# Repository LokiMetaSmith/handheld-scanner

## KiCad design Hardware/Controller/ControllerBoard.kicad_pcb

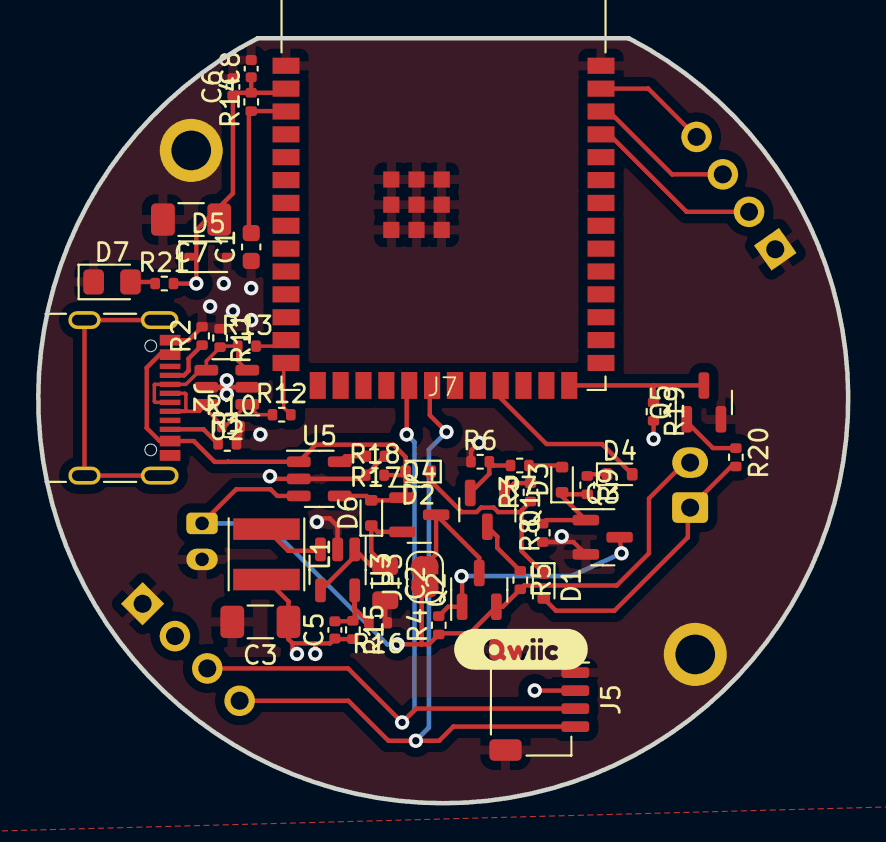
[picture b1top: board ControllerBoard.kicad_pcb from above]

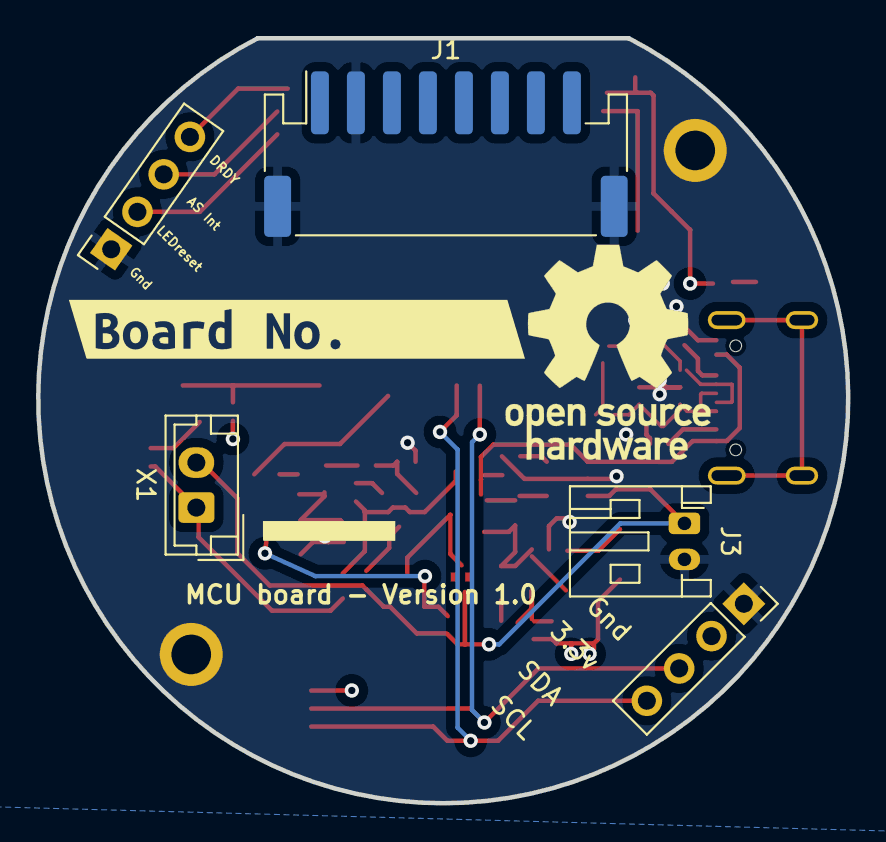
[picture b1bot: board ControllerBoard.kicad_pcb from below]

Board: 4 copper layers, 45.0 x 42.5 mm, 56 parts (6 on the bottom side), 34 nets.

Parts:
C1: 2u; C_0603_1608Metric
C2: 4.7u; C_0805_2012Metric
C3, C7: 10u; C_1206_3216Metric_Pad1.33x1.80mm_HandSolder
C5: 6.8p; C_0402_1005Metric
C6: 0.01u; C_0402_1005Metric
C8: 0.1u; C_0402_1005Metric
D1, D2, D3, D4, D6: BAS516; D_SOD-523
D5: 3.3v_TVS; D_SOD-323
D7: POWER LED; LED_0805_2012Metric_Pad1.15x1.40mm_HandSolder
J1: Conn_01x08_MountingPin; JST_PH_S8B-PH-SM4-TB_1x08-1MP_P2.00mm_Horizontal
J2: USB_C_Receptacle_USB2.0; USB_C_Receptacle_GCT_USB4105-xx-A_16P_TopMnt_Horizontal
J3: Conn_01x02_Male; JST_PH_S2B-PH-K_1x02_P2.00mm_Horizontal
J5: I2C; JST_SH_SM04B-SRSS-TB_1x04-1MP_P1.00mm_Horizontal
J7: Conn_01x09; round_notch
JP3: Jumper_2_Open; SolderJumper-2_P1.3mm_Bridged2Bar_RoundedPad1.0x1.5mm
L1: 2.2uH; L_Taiyo-Yuden_MD-4040
LOGO1: OSHW-Logo_11.4x12mm_SilkScreen
LOGO2: PlasticScannerLogo
Q1, Q3, Q5: BC818; SOT-23
Q2, Q4: AO3401A; SOT-23
R1, R2, R17: 5.1k; R_0402_1005Metric
R3, R20, R21: 1k; R_0402_1005Metric
R4, R8, R18: 100k; R_0402_1005Metric
R5, R7: 10k; R_0402_1005Metric
R6: 220k; R_0402_1005Metric
R9: 220; R_0402_1005Metric
R10, R11: 15K; R_0402_1005Metric
R12, R13: 27; R_0402_1005Metric
R14, R19: 10K; R_0402_1005Metric
R15: 680k; R_0402_1005Metric
R16: 150K; R_0402_1005Metric
U1: ESP32-S3-WROOM-1
U2: SN65220; SOT-23-6
U3: TLV62569DBV; SOT-23-5
U5: MCP73811T-420I-OT; SOT-23-5
X1: CON_JST_PH_2PIN_MTPH2; JST_EH_B2B-EH-A_1x02_P2.50mm_Vertical
kibuzzard-6398DD41: G***; kibuzzard-6398DD41
kibuzzard-6346913B: G***; kibuzzard-6346913B

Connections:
+3V3: C3.1, C5.1, C6.1, C7.1, C8.1, D5.1 (A1), J5.2, J7.2, L1.2, R14.2, R15.2, R19.2, R21.2, U1.2 (3V3)
/AS7341_INT: J7.7, U1.38 (GPIO2/TOUCH2/ADC1_CH1)
/D+: J2.A6 (D+), J2.B6 (D+), R10.1, R12.1, U2.1, U2.6 (A)
/D-: J2.A7 (D-), J2.B7 (D-), R11.2, R13.1, U2.3, U2.4 (B)
/DRDY_INT: J7.8, U1.39 (GPIO1/TOUCH1/ADC1_CH0)
/EN: C1.2, R14.1, U1.3 (EN)
/KeepAlive: D4.2 (A), U1.23 (GPIO21)
/LED_RESET: J7.6, U1.37 (U0TXD/GPIO43/CLK_OUT1)
/Switched_Power: C2.1, D6.1 (K), Q4.2 (S), U3.1 (EN), U3.4 (VIN)
/Trigger: Q5.2 (E), R19.1, U1.26 (GPIO45)
/Trigger_Wake_Up/VBAT: J3.1, JP3.1 (A), Q2.2 (S), R4.1, R5.2, U5.3 (VBAT), X1.2
/USB_D+: R12.2, U1.14 (GPIO20/U1CTS/ADC2_CH9/CLK_OUT1/USB_D+)
/USB_D-: R13.2, U1.13 (GPIO19/U1RTS/ADC2_CH8/CLK_OUT2/USB_D-)
/USB_pwr: D2.2 (A), D6.2 (A), J2.A4 (VBUS), J2.A9 (VBUS), J2.B4 (VBUS), J2.B9 (VBUS), Q4.1 (G), R18.2, U5.1 (CEN), U5.4 (VDD)
GND: C1.1, C2.2, C3.2, C6.2, C7.2, C8.2, D5.2 (A2), D7.1 (K), J1.2, J1.MP (MountPin), J2.A1 (GND), J2.A12 (GND), J2.B1 (GND), J2.B12 (GND), J3.2, J5.1, J5.MP (Pin_5), J7.1, J7.5, J7.MP, Q3.2 (E), Q5.1 (B), R1.2, R2.2, R6.1, R8.1, R10.2, R11.1, R16.1, R17.1, R18.1, U1.1 (GND), U1.40 (GND), U1.41 (GND), U2.2 (GND), U2.5 (GND), U3.2 (GND), U5.2 (VSS)
unnamed: D1.2 (A), R20.1, X1.1
unnamed: D1.1 (K), D2.1 (K), R3.1
unnamed: D3.2 (A), R7.1
unnamed: D3.1 (K), Q3.1 (B), R8.2, R9.2
unnamed: D4.1 (K), R9.1
unnamed: D7.2 (A), R21.1
unnamed: J2.A5 (CC1), R2.1
unnamed: J2.B5 (CC2), R1.1
unnamed: JP3.2 (B), Q2.3 (D), Q4.3 (D)
unnamed: Q1.1 (B), R3.2
unnamed: Q1.3 (C), R5.1
unnamed: Q1.2 (E), R6.2, R7.2
unnamed: Q2.1 (G), Q3.3 (C), R4.2
unnamed: Q5.3 (C), R20.2
unnamed: C5.2, R15.1, R16.2, U3.5 (FB)
unnamed: L1.1, U3.3 (SW)
unnamed: R17.2, U5.5 (PROG)
SCL: J5.4, J7.4, U1.20 (GPIO12/TOUCH12/ADC2_CH1/FSPICLK/FSPIIO6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)
SDA: J5.3, J7.3, U1.19 (GPIO11/TOUCH11/ADC2_CH0/FSPID/FSPIIO5/S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)

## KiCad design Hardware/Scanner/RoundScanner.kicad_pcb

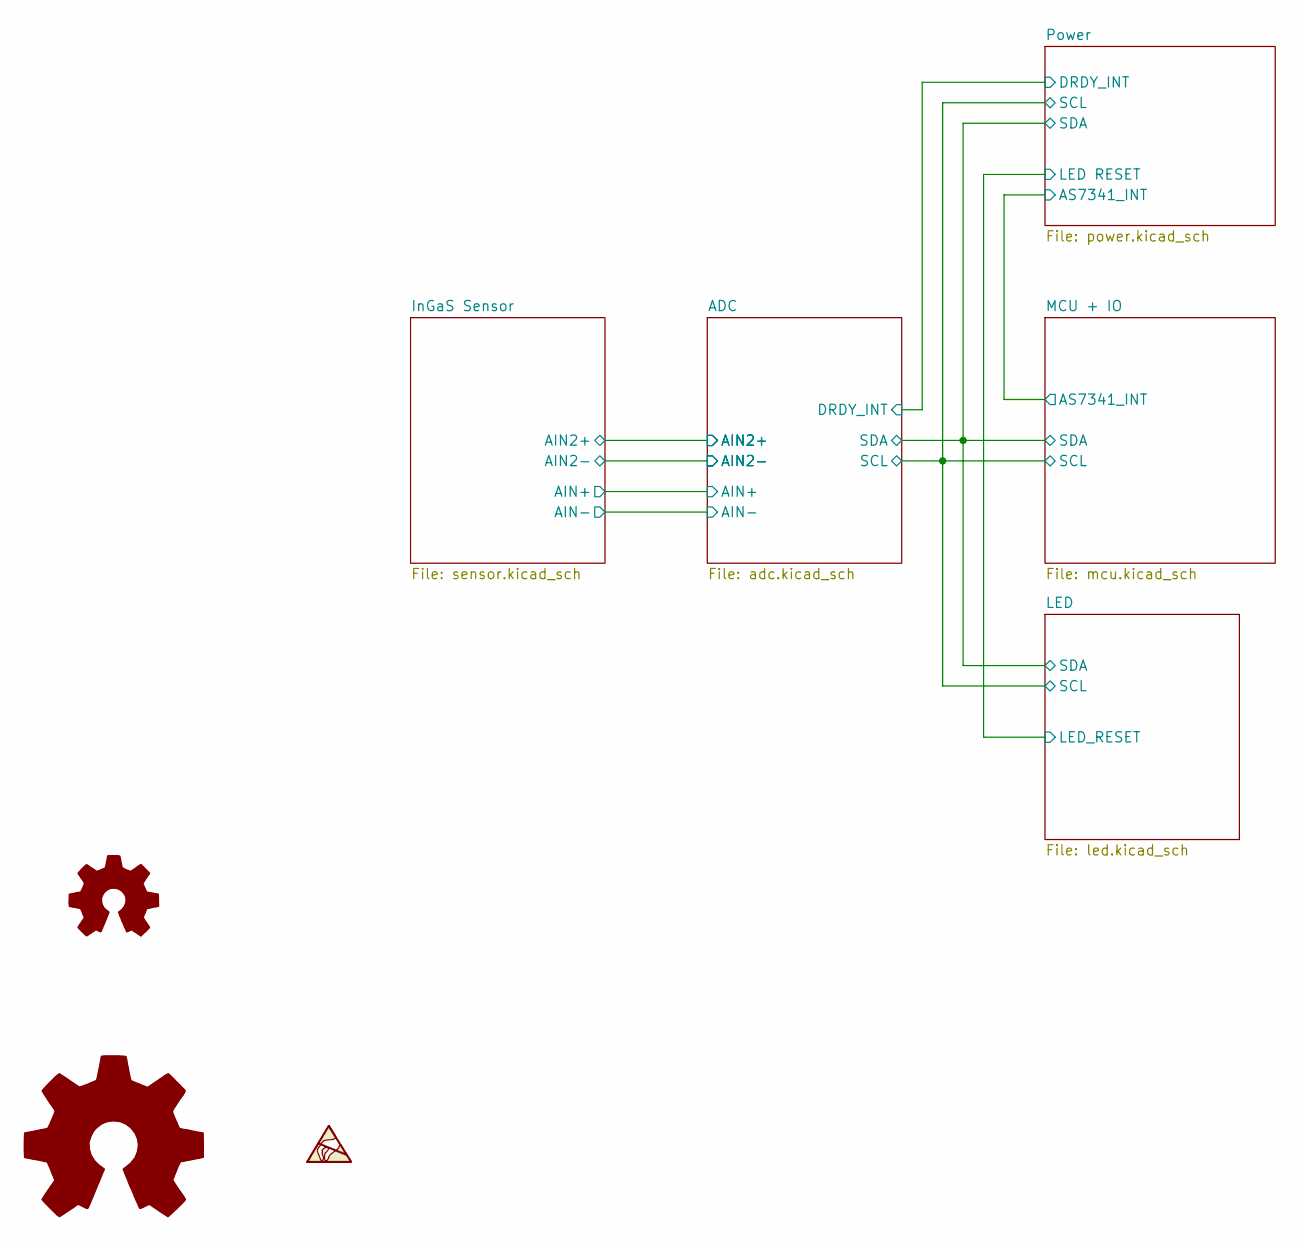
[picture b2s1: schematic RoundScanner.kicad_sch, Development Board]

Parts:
LOGO1: OSHW-Logo_11.4x12mm_SilkScreen
LOGO2: PlasticScannerLogo

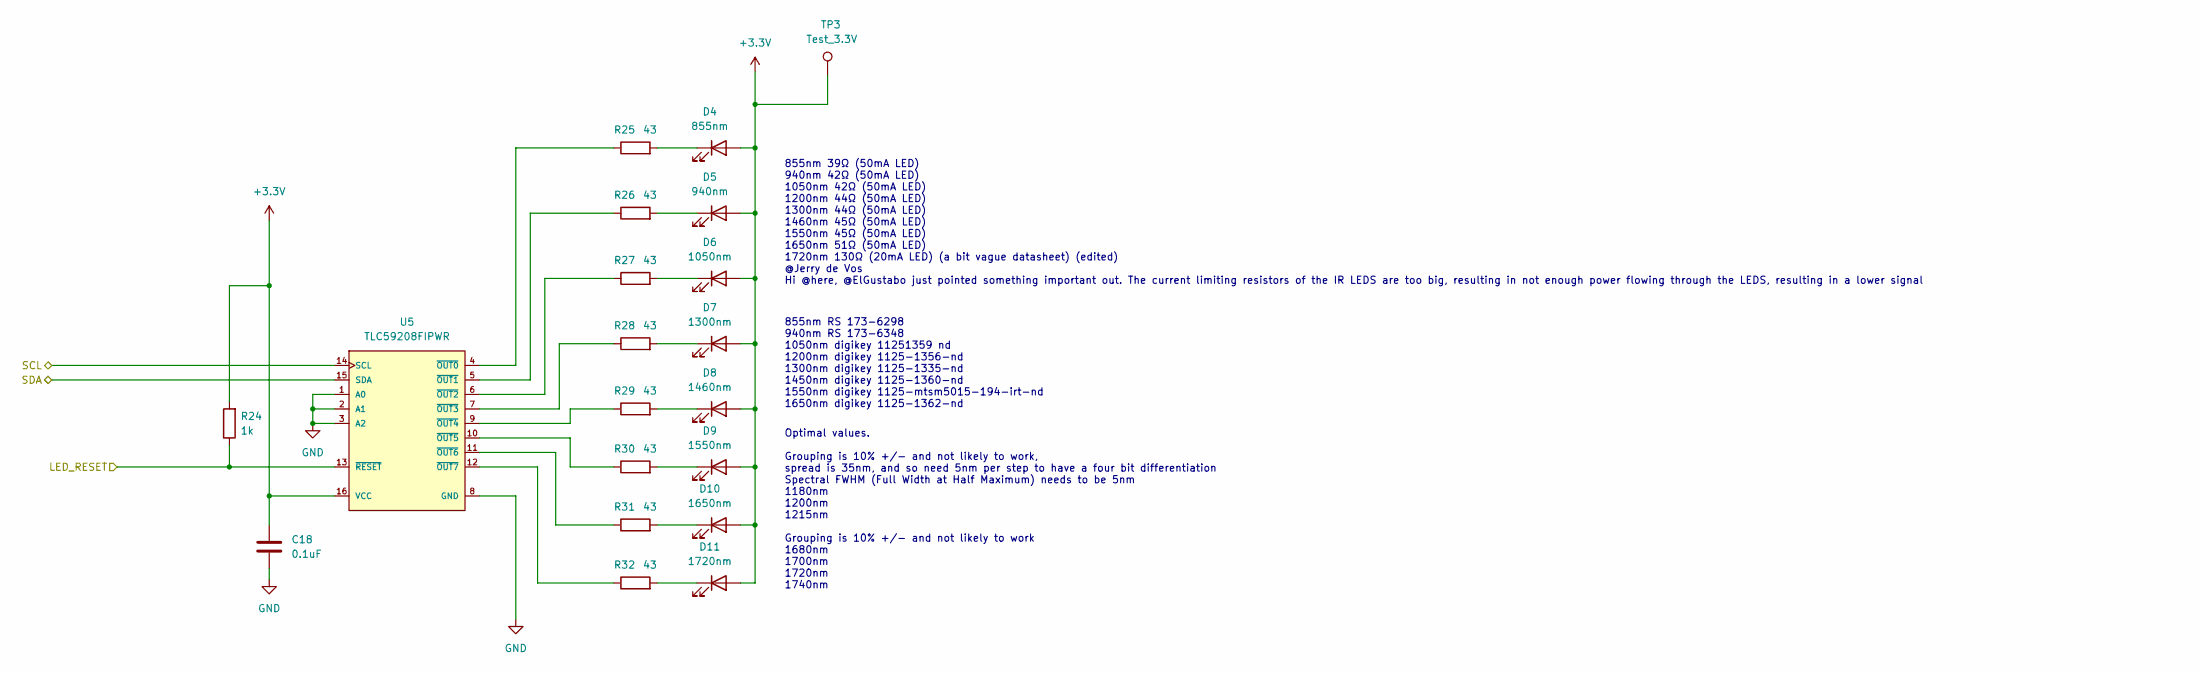
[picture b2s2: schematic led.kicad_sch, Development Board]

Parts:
C18: 0.1uF; C_0603_1608Metric_Pad1.08x0.95mm_HandSolder; digikey description CAP CER 0.1UF 16V X7R 0603
D4: 855nm; LED_1206_3216Metric_Pad1.42x1.75mm_HandSolder; digikey part number 1516-1269-1-ND
D5: 940nm; LED_1206_3216Metric_Pad1.42x1.75mm_HandSolder; digikey part number 1080-1350-1-ND
D6: 1050nm; LED_1206_3216Metric_Pad1.42x1.75mm_HandSolder; digikey part number 1125-1342-ND
D7: 1300nm; LED_1206_3216Metric_Pad1.42x1.75mm_HandSolder; digikey part number 5242-OIS-1501300N-X-TCT-ND
D8: 1460nm; LED_1206_3216Metric_Pad1.42x1.75mm_HandSolder; digikey part number 1125-MTSM6014-194-IRCT-ND
D9: 1550nm; LED_1206_3216Metric_Pad1.42x1.75mm_HandSolder; digikey part number 5242-OIS-1501550N-X-TCT-ND
D10: 1650nm; LED_1206_3216Metric_Pad1.42x1.75mm_HandSolder; digikey part number 1125-1354-ND
D11: 1720nm; LED_1206_3216Metric_Pad1.42x1.75mm_HandSolder; digikey part number 1125-MTSM0012-194-IRCT-ND
R24: 1k; R_0603_1608Metric_Pad0.98x0.95mm_HandSolder; digikey description RES 1K OHM 1% 1/10W 0603
R25, R26, R27, R28, R29, R30, R31: 43; R_0603_1608Metric_Pad0.98x0.95mm_HandSolder; digikey description RES SMD 43 OHM 5% 1/3W 0603
R32: 43; R_0603_1608Metric_Pad0.98x0.95mm_HandSolder; mouser part number 667-ERJ-3EKF1300V; digikey description RES SMD 43 OHM 5% 1/3W 0603
TP3: Test_3.3V; TestPoint_Pad_D1.5mm
U5: TLC59208FIPWR; SOP65P640X120-16N; digikey description TLC59208FIPWR

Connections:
/LED/LED_RESET: R24.1, U5.13 (~RESET); also elsewhere on the board
GND: C18.2, U5.1 (A0), U5.2 (A1), U5.3 (A2), U5.8 (GND); also elsewhere on the board
unnamed: D4.1 (K), R25.2
unnamed: D5.1 (K), R26.2
unnamed: D6.1 (K), R27.2
unnamed: D7.1 (K), R28.2
unnamed: D8.1 (K), R29.2
unnamed: D9.1 (K), R30.2
unnamed: D10.1 (K), R31.2
unnamed: D11.1 (K), R32.2
unnamed: R25.1, U5.4 (~OUT0)
unnamed: R26.1, U5.5 (~OUT1)
unnamed: R27.1, U5.6 (~OUT2)
unnamed: R28.1, U5.7 (~OUT3)
unnamed: R29.1, U5.9 (~OUT4)
unnamed: R30.1, U5.10 (~OUT5)
unnamed: R31.1, U5.11 (~OUT6)
unnamed: R32.1, U5.12 (~OUT7)
SCL: U5.14 (SCL); also elsewhere on the board
SDA: U5.15 (SDA); also elsewhere on the board

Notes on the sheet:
855nm RS 173-6298 940nm RS 173-6348 1050nm digikey 11251359 nd 1200nm digikey 1125-1356-nd 1300nm digikey 1125-1335-nd 1450nm digikey 1125-1360-nd 1550nm digikey 1125-mtsm5015-194-irt-nd 1650nm digikey 1125-1362-nd
855nm 39Ω (50mA LED) 940nm 42Ω (50mA LED) 1050nm 42Ω (50mA LED) 1200nm 44Ω (50mA LED) 1300nm 44Ω (50mA LED) 1460nm 45Ω (50mA LED) 1550nm 45Ω (50mA LED) 1650nm 51Ω (50mA LED) 1720nm 130Ω (20mA LED) (a bit vague datasheet) (edited) @Jerry de Vos Hi @here, @ElGustabo just pointed something important o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
Optimal values. Grouping is 10% +/- and not likely to work, spread is 35nm, and so need 5nm per step to have a four bit differentiation Spectral FWHM (Full Width at Half Maximum) needs to be 5nm 1180nm 1200nm 1215nm Grouping is 10% +/- and not likely to work 1680nm 1700nm 1720nm 1740nm

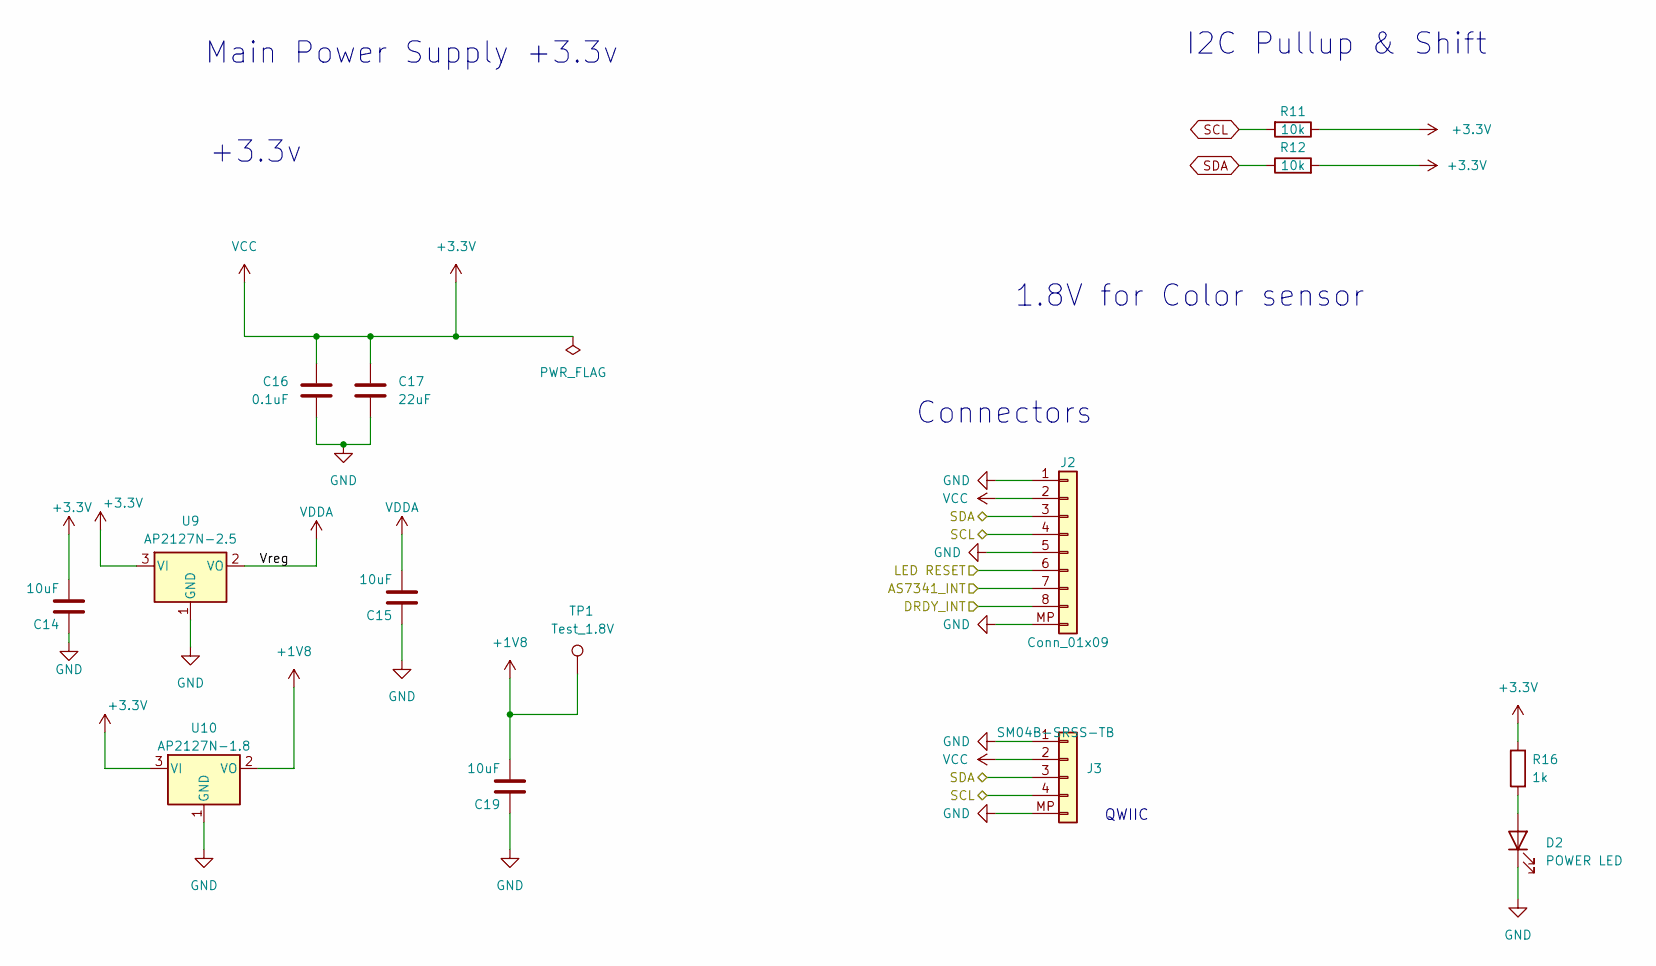
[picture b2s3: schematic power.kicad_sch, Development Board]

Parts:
C14, C15, C19: 10uF; C_0603_1608Metric_Pad1.08x0.95mm_HandSolder; digikey description CAP CER 10UF 6.3V X5R 0603
C16: 0.1uF; C_0603_1608Metric_Pad1.08x0.95mm_HandSolder; digikey description CAP CER 0.1UF 16V X7R 0603
C17: 22uF; C_0603_1608Metric_Pad1.08x0.95mm_HandSolder; digikey description CAP CER 22UF 6.3V X5R 0603
D2: POWER LED; LED_0805_2012Metric_Pad1.15x1.40mm_HandSolder; digikey description LED RED CLEAR 1206 SMD
J2: Conn_01x09; round_notch
J3: SM04B-SRSS-TB; JST_SH_SM04B-SRSS-TB_1x04-1MP_P1.00mm_Horizontal; digikey description SM04B-SRSS-TB
R11, R12: 10k; R_0603_1608Metric_Pad0.98x0.95mm_HandSolder; mouser part number 279-CRGH0603J10K; mouser description CRGH0603J10K
R16: 1k; R_0603_1608Metric_Pad0.98x0.95mm_HandSolder; digikey description RES 1K OHM 1% 1/10W 0603
TP1: Test_1.8V; TestPoint_Pad_D1.5mm
U9: AP2127N-2.5; SOT-23; digikey description IC REG LINEAR 2.5V 300MA SOT23
U10: AP2127N-1.8; SOT-23; digikey description IC REG LINEAR 1.8V 300MA SOT23-3

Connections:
+1V8: C19.2, TP1.1, U10.2 (VO); also elsewhere on the board
/ADC/DRDY_INT: J2.8; also elsewhere on the board
/LED/LED_RESET: J2.6; also elsewhere on the board
/MCU + IO/AS7341_INT: J2.7; also elsewhere on the board
GND: C14.1, C15.1, C16.1, C17.2, C19.1, D2.1 (K), J2.1, J2.5, J2.MP, J3.1, J3.MP (Pin_5), U9.1 (GND), U10.1 (GND); also elsewhere on the board
unnamed: D2.2 (A), R16.2
SCL: J2.4, J3.4, R11.2; also elsewhere on the board
SDA: J2.3, J3.3, R12.1; also elsewhere on the board
VDDA: C15.2, U9.2 (VO); also elsewhere on the board

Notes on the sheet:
Connectors
QWIIC
Main Power Supply +3.3v
1.8V for Color sensor
+3.3v
I2C Pullup & Shift

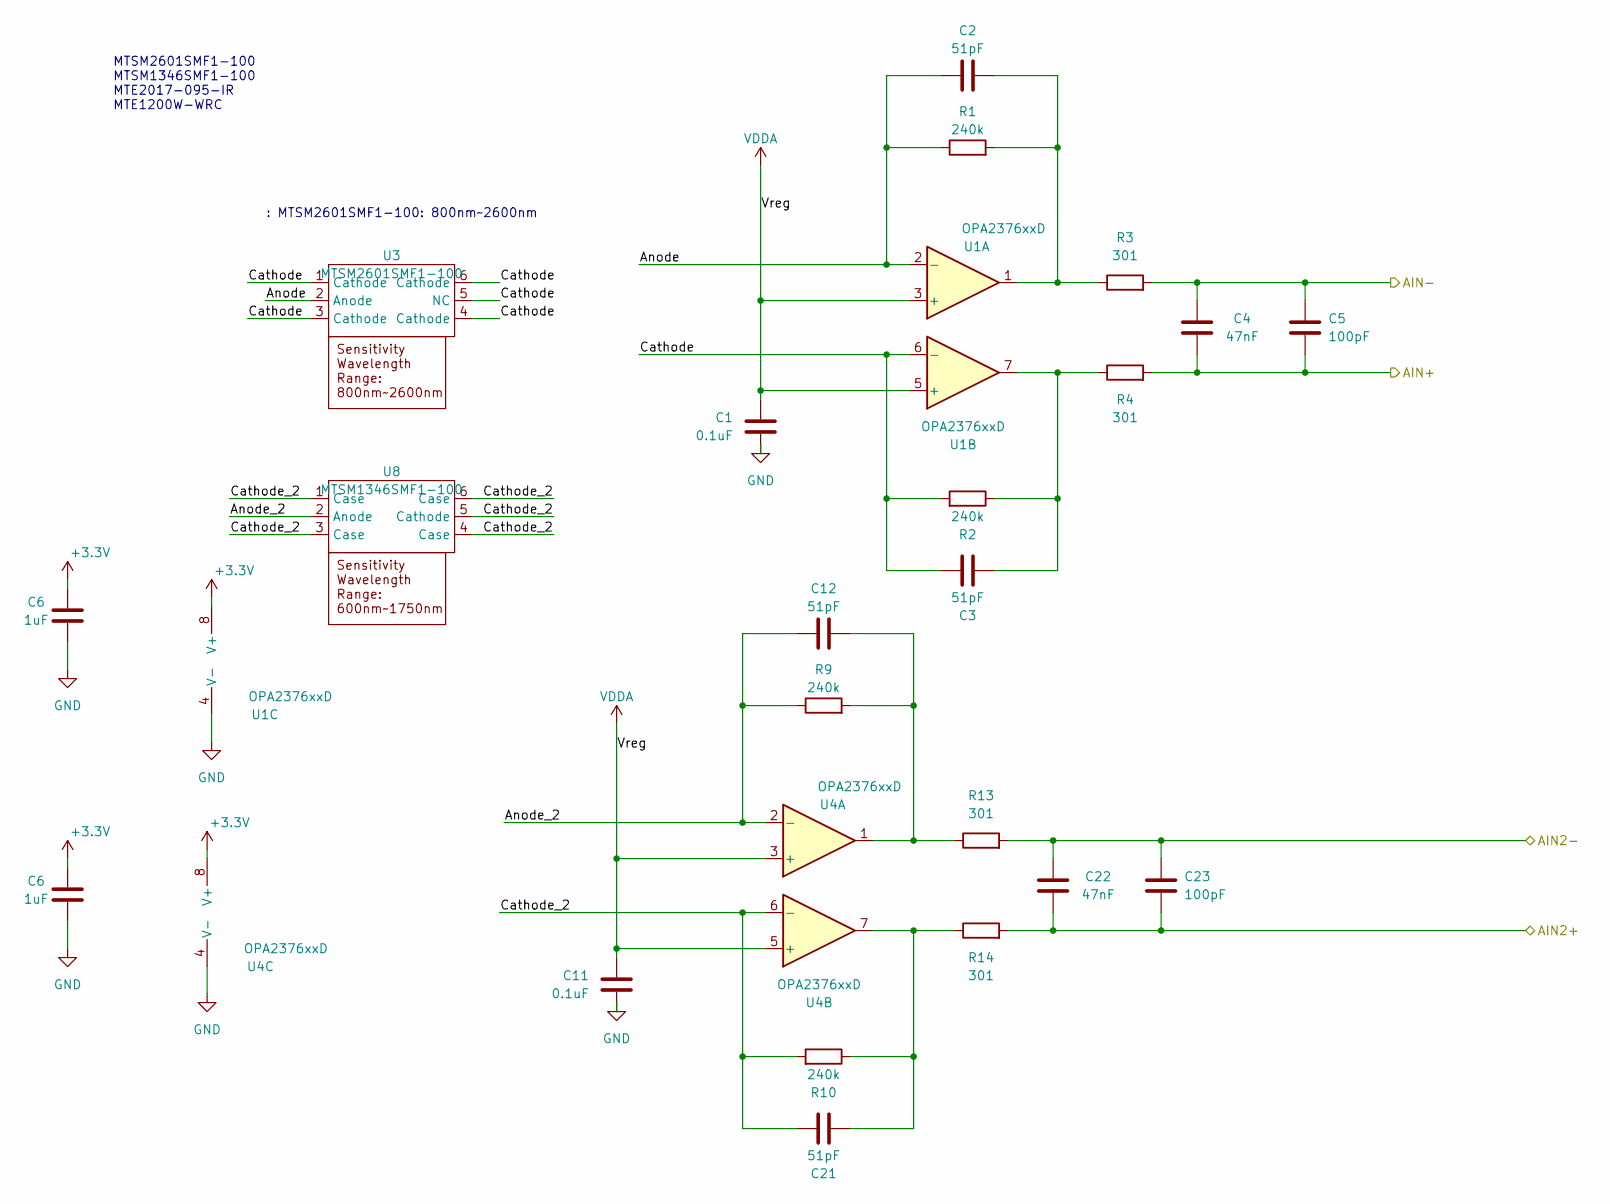
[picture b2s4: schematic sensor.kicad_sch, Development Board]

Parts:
C1, C11: 0.1uF; C_0603_1608Metric_Pad1.08x0.95mm_HandSolder; digikey description CAP CER 0.1UF 16V X7R 0603
C2, C3, C12, C21: 51pF; C_0603_1608Metric_Pad1.08x0.95mm_HandSolder; digikey description CAP CER 51PF 50V C0G/NP0 0603
C4, C22: 47nF; C_0603_1608Metric_Pad1.08x0.95mm_HandSolder; digikey description CAP CER 0.047UF 50V X7R 0603
C5, C23: 100pF; C_0603_1608Metric_Pad1.08x0.95mm_HandSolder; digikey description CAP CER 100PF 50V C0G/NP0 0603
C6: 1uF; C_0603_1608Metric_Pad1.08x0.95mm_HandSolder; digikey description CAP CER 1UF 16V X7R 0603
R1, R2, R9, R10: 240k; R_0603_1608Metric_Pad0.98x0.95mm_HandSolder; mouser part number 667-ERJ-3EKF2403V; mouser description ERJ-3EKF2403V
R3, R4, R13, R14: 301; R_0603_1608Metric_Pad0.98x0.95mm_HandSolder; mouser part number 667-ERJ-3EKF3010V; mouser description ERJ-3EKF3010V
U1, U4: OPA2376xxD; SOIC127P599X175-8N; mouser part number 595-OPA2376AIDR; digikey part number 296-26263-5-ND
U3: MTSM2601SMF1-100; digikey description SENSOR PHOTODIODE 800-2600NM SMD
U8: MTSM1346SMF1-100; digikey description SENSOR PHOTODIODE 1300NM 6SMD

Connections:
/ADC/AIN2+: C22.1, C23.2, R14.2; also elsewhere on the board
/ADC/AIN2-: C22.2, C23.1, R13.2; also elsewhere on the board
/ADC/AIN+: C4.1, C5.2, R4.2; also elsewhere on the board
/ADC/AIN-: C4.2, C5.1, R3.2; also elsewhere on the board
/InGaS Sensor/Anode: C2.1, R1.1, U1.2 (-), U3.2 (Anode)
/InGaS Sensor/Anode_2: C12.1, R9.1, U4.2 (-), U8.2 (Anode)
/InGaS Sensor/Cathode: C3.1, R2.2, U1.6 (-), U3.1 (Cathode), U3.3 (Cathode), U3.4 (Cathode), U3.5 (NC), U3.6 (Cathode)
/InGaS Sensor/Cathode_2: C21.1, R10.2, U4.6 (-), U8.1 (Case), U8.3 (Case), U8.4 (Case), U8.5 (Cathode), U8.6 (Case)
GND: C1.1, C6.1, C11.1, U1.4 (V-), U4.4 (V-); also elsewhere on the board
unnamed: C2.2, R1.2, R3.1, U1.1
unnamed: C3.2, R2.1, R4.1, U1.7
unnamed: C12.2, R9.2, R13.1, U4.1
unnamed: C21.2, R10.1, R14.1, U4.7
VDDA: C1.2, C11.2, U1.3 (+), U1.5 (+), U4.3 (+), U4.5 (+); also elsewhere on the board

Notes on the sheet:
MTSM2601SMF1-100 MTSM1346SMF1-100 MTE2017-095-IR MTE1200W-WRC
: MTSM2601SMF1-100: 800nm~2600nm

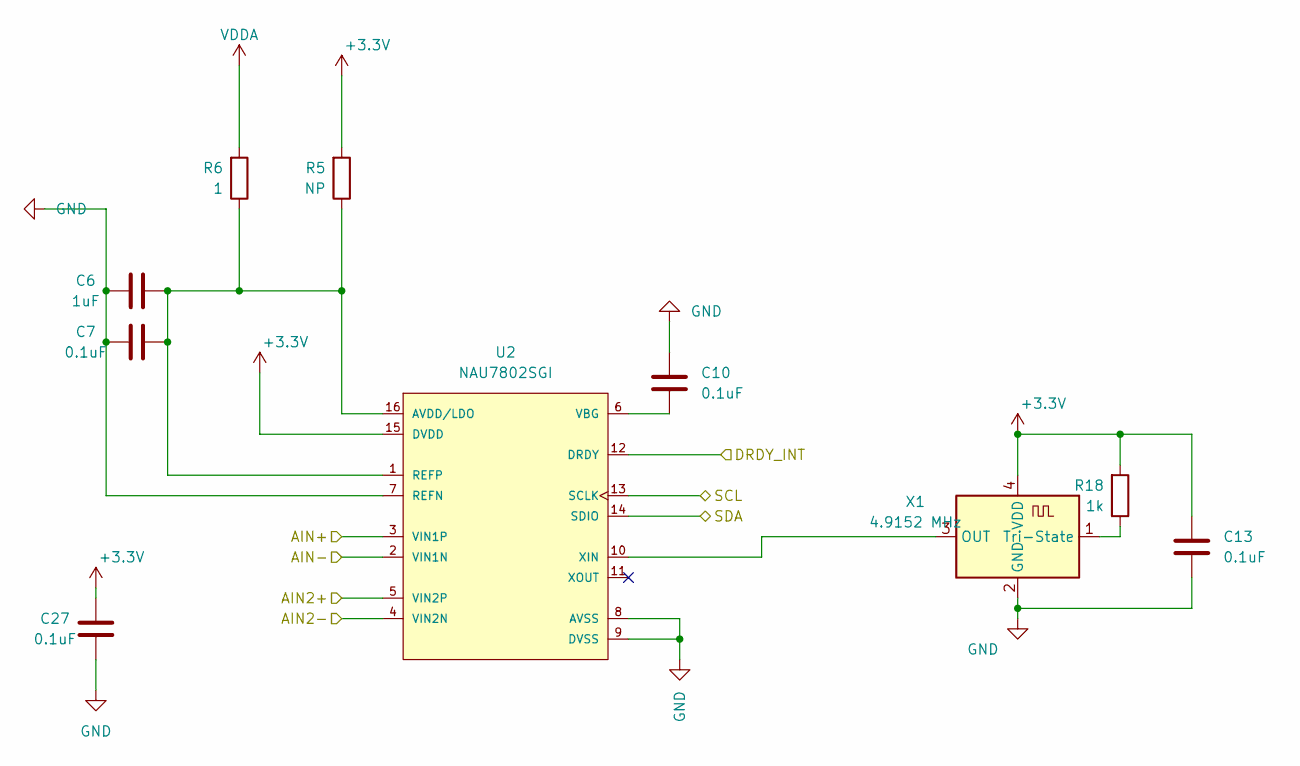
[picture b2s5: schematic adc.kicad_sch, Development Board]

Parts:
C6: 1uF; C_0603_1608Metric_Pad1.08x0.95mm_HandSolder; digikey description CAP CER 1UF 16V X7R 0603
C7, C10, C13, C27: 0.1uF; C_0603_1608Metric_Pad1.08x0.95mm_HandSolder; digikey description CAP CER 0.1UF 16V X7R 0603
R5: NP; R_0603_1608Metric_Pad0.98x0.95mm_HandSolder
R6: 1; R_0603_1608Metric_Pad0.98x0.95mm_HandSolder; mouser part number 652-CHP0603QFW-1R00E; mouser description CHP0603QFW-1R00ELF
R18: 1k; R_0603_1608Metric_Pad0.98x0.95mm_HandSolder; digikey description RES 1K OHM 1% 1/10W 0603
U2: NAU7802SGI; Nuvoton-NAU7802SGI; digikey description IC ADC 24BIT I2C/SRL 16-SOP
X1: 4.9152 MHz; Oscillator_SMD_ECS_2520MV-xxx-xx-4Pin_2.5x2.0mm; digikey description XTAL OSC XO 4.9152MHZ CMOS SMD

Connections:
/ADC/AIN2+: U2.5 (VIN2P); also elsewhere on the board
/ADC/AIN2-: U2.4 (VIN2N); also elsewhere on the board
/ADC/AIN+: U2.3 (VIN1P); also elsewhere on the board
/ADC/AIN-: U2.2 (VIN1N); also elsewhere on the board
/ADC/DRDY_INT: U2.12 (DRDY); also elsewhere on the board
GND: C6.1, C7.1, C10.1, C13.2, C27.1, U2.7 (REFN), U2.8 (AVSS), U2.9 (DVSS), X1.2 (GND); also elsewhere on the board
unnamed: C10.2, U2.6 (VBG)
unnamed: U2.10 (XIN), X1.3 (OUT)
unnamed: R18.1, X1.1 (Tri-State)
SCL: U2.13 (SCLK); also elsewhere on the board
SDA: U2.14 (SDIO); also elsewhere on the board
VDDA: R6.2; also elsewhere on the board

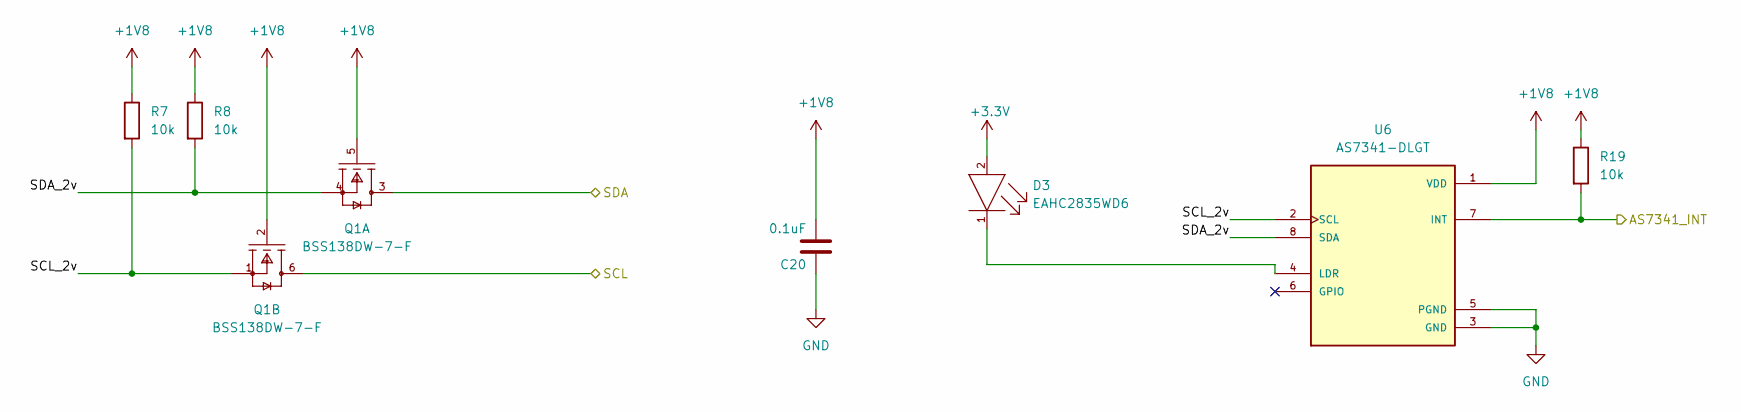
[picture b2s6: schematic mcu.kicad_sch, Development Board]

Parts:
C20: 0.1uF; C_0603_1608Metric_Pad1.08x0.95mm_HandSolder; digikey description CAP CER 0.1UF 16V X7R 0603
D3: EAHC2835WD6; Everlight-EAHC2835WD6-MFG; mouser part number 638-EAHC2835WD6; digikey description LED COOL WHITE 6500K 2SMD
Q1: BSS138DW-7-F; Diodes_Inc._-_BSS138DW-7-F-A; mouser part number 621-BSS138DW-F; digikey description MOSFET 2N-CH 50V 0.2A SC70-6
R7, R8, R19: 10k; R_0603_1608Metric_Pad0.98x0.95mm_HandSolder; mouser part number 279-CRGH0603J10K; mouser description CRGH0603J10K
U6: AS7341-DLGT; PSON80P310X200X110-8N; PARTREV V3; digikey description SENSOR OPT AMBIENT 8OLGA

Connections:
+1V8: C20.2, Q1.2 (G2), Q1.5 (G1), R7.1, R8.1, R19.1, U6.1 (VDD); also elsewhere on the board
/MCU + IO/AS7341_INT: R19.2, U6.7 (INT); also elsewhere on the board
/MCU + IO/SCL_2v: Q1.1 (S2), R7.2, U6.2 (SCL)
/MCU + IO/SDA_2v: Q1.4 (S1), R8.2, U6.8 (SDA)
GND: C20.1, U6.3 (GND), U6.5 (PGND); also elsewhere on the board
unnamed: D3.1 (CATHODE), U6.4 (LDR)
SCL: Q1.6 (D2); also elsewhere on the board
SDA: Q1.3 (D1); also elsewhere on the board

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
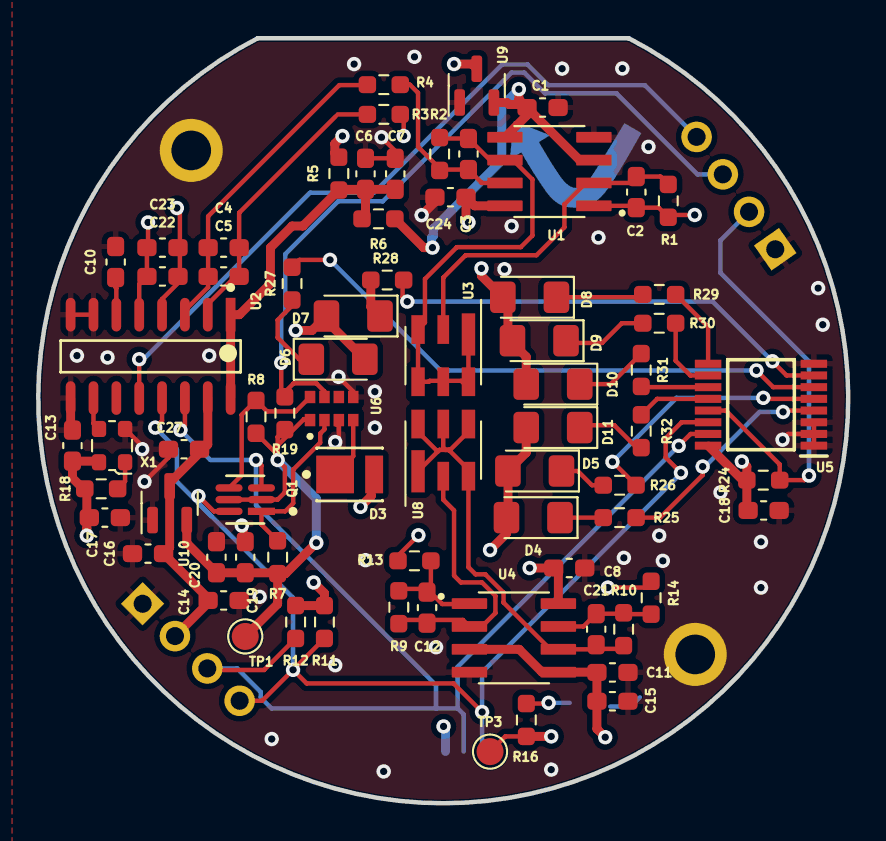
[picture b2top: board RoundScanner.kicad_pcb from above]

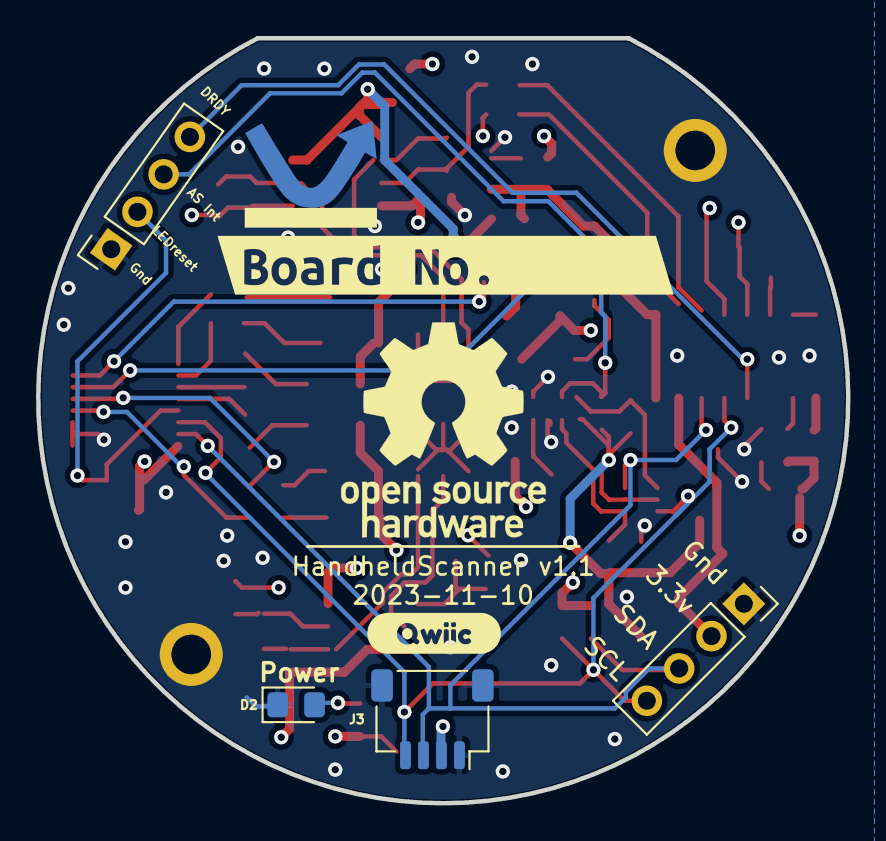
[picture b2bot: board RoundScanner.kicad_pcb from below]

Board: 4 copper layers, 45.0 x 42.5 mm, 79 parts (6 on the bottom side), 45 nets.

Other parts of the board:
C8, C24: 1uF; C_0603_1608Metric_Pad1.08x0.95mm_HandSolder
kibuzzard-6398DD41: G***; kibuzzard-6398DD41
kibuzzard-6346913B: G***; kibuzzard-6346913B

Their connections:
GND: C8.1, C24.1; also elsewhere on the board

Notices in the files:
parts and their libraries:
Copyright 2021 Accelerated Designs. All rights reserved.
